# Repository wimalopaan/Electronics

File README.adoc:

= RC Electronics
Wilhelm Meier <wilhelm.wm.meier@googlemail.com>
:toc:
:toclevels: 5
:numbered:
:sectnums:
:sectnumlevels: 5
:toc-placement!:
:tip-caption: :bulb:
:note-caption: :information_source:
:important-caption: :heavy_exclamation_mark:
:caution-caption: :fire:
:warning-caption: :warning:
  
:ddir: https://wimalopaan.github.io/Electronics
:rcb: {ddir}/rc/boards

*English* | <<README.de.adoc#,Deutsch>>

image::images/logo/Logo.png[width=50%]

[NOTE]
--
This page and the accompanying repositories are mostly for my rc (radio controlled models) electronics including EdgeTx/OpenTx and ExpressLRS addons, LUA-scripting, videos, and more.
--

[WARNING]
--
No AI generated code inside, all errors are human!
--

:toclevels: 2
toc::[]

== Foreword

[NOTE]
.To the german readers
--
Die alte Seite ist noch (und bleibt auch) als <<Old.adoc#,Old.adoc>> verfügbar.
--

[[ieee]]
== IEEE: the RC software compound (stack)

Using `EdgeTx`, `ExpressLRS` and `ESCape32` is _the_ combination of RC related open-source software projects that I use 
now in all my crafts. 

[NOTE]
--
The three big `E`s: `EdgeTx`, `ExpressLRS` and `ESCape32` 
--

If I need something like _return-to-home_ I would choose clearly `INAV`. 
So, putting all together, you get `EEEI`.

[IMPORTANT]
--
If you push `EdgeTx`, `ExpressLRS`, `ESCape32` and `INAV` onto a stack, pop them off and take their first character, 
you'll get `IEEE`, the *RC software stack* (please do not confuse with https://www.ieee.org[], that's another crucial thing ;-) ).
--

[[documents]]
== Documents

The content of this page is split into the following documents. The <<detailed_toc>> lists every section with a direct link. The <<project-status>> shows the state of every project. All videos are listed in <<docs/videos.adoc#,Videos by project>>.

=== Software, firmware and protocols

[cols="1,3a",options="header"]
|===
| Document | Contents

| <<docs/edgetx.adoc#,EdgeTx>>
| Extensions and pull-requests for the EdgeTx radio firmware:

* <<docs/edgetx.adoc#edgetx-proc,EdgeTx processing>>
* <<docs/edgetx.adoc#vcontrols,Virtual Controls for EdgeTx>>
* <<docs/edgetx.adoc#edgetx_32channels,32-Channels extension for the CRSF-Protocol>>
* <<docs/edgetx.adoc#edgetx_shm_bw,SHM-Variables for B&W radios>>
* <<docs/edgetx.adoc#crsf_batt_id,Enhanced Parser for instance-id augmented CRSF BATT-sensor frames>>
* <<docs/edgetx.adoc#edgetx_custom_moved,Custom EdgeTx builds>>

| <<docs/elrs.adoc#,ExpressLRS>>
| ExpressLRS: features, modules, receivers and my modifications (V3/V4):

* <<docs/elrs.adoc#_expresslrs_for_short_range_radio_control,ExpressLRS for short range radio control>>
* <<docs/elrs.adoc#_expresslrs_modules_and_receivers,ExpressLRS: modules and receivers>>
* <<docs/elrs.adoc#_multiple_elrs_receivers_bound_to_one_elrs_module,Multiple ELRS-receivers bound to one ELRS-module>>
* <<docs/elrs.adoc#_32_channels_for_elrs,32-channels for ELRS>>
* <<docs/elrs.adoc#elrs-matrix,Feature matrix>>
* <<docs/elrs.adoc#elrs-mods,ELRS modifications and pull-requests>>
* <<docs/elrs.adoc#elrs-relay,ELRS relay configuration>>

| <<docs/protocols.adoc#,Protocols>>
| CRSF protocol extensions (MultiSwitch, Prop32, ESP-NOW), CRSF half-duplex bus, Hardware-Extension-Protocol:

* <<docs/protocols.adoc#crsf_sw,Proposal for the CRSF protocol>>
* <<docs/protocols.adoc#crsf-bus,CRSF-Half-Duplex Bus>>
* <<docs/protocols.adoc#hwext,Hardware-Extension-Protocol>>
* <<docs/protocols.adoc#hwlua,LUA-script for the Hardware-Extension-Protocol>>

| <<docs/escape32.adoc#,ESCape32: firmware for a family of small/medium BLDC (and brushed) motor controller (brushless/brushed ESC)>>
| ESCape32 firmware for small/medium BLDC (and brushed) ESCs and my modifications:

* <<docs/escape32.adoc#_sine_startup,Sine startup>>
* <<docs/escape32.adoc#_modifications,Modifications>>
* <<docs/escape32.adoc#_hardware,Hardware>>
* <<docs/escape32.adoc#_info,Info>>

| <<docs/inav.adoc#,INAV: Navigation-enabled flight control software>>
| INAV and the self-balancing robot Mortimer.

| <<docs/flysky.adoc#,FlySky FS-i6X / FS-i6S>>
| Alternative firmware for FlySky FS-i6X/FS-i6S (Rust and C++), ELRS for the FS-i6X, Openix6:

* <<docs/flysky.adoc#flysky-i6x-rs,FlySky-I6X-rs: an alternative firmware for the FlySky FS-I6X transmitter>>
* <<docs/flysky.adoc#flysky-i6s-rs,FlySky-I6S-rs: an alternative firmware for the FlySky FS-I6S transmitter>>
* <<docs/flysky.adoc#i6s-cpp,i6s-cpp: a C++26 port of the FlySky-I6X-rs / FlySky-I6S-rs firmware>>
* <<docs/flysky.adoc#elrs_i6x,ELRS for the FlySky-I6X>>
* <<docs/flysky.adoc#oix6,Openix6>>

| <<docs/building.adoc#,Building firmware>>
| Compiling my projects (`wmucpp`), EdgeTx, ExpressLRS and ESCape32 with `github` codespaces:

* <<docs/building.adoc#gitpod_wm,Compiling the source code of my projects (`wmucpp`)>>
* <<docs/building.adoc#edgetx_custom,Custom EdgeTx builds>>
* <<docs/building.adoc#build_elrs,ExpressLRS>>
* <<docs/building.adoc#build_escape32,ESCape32>>

|===

=== Projects (hardware and firmware)

[cols="1,3a",options="header"]
|===
| Document | Contents

| <<docs/multiswitch.adoc#,MultiSwitch>>
| ELRS/CRSF MultiSwitch modules, <<docs/multiswitch.adoc#msw_widget_ng,MultiSwitch NG Widget>>, stable MultiSwitch Widget and telemetry script.

| <<docs/crsf-devices.adoc#,CRSF devices>>
| LED 4x4, CRSF-Switch/Router, MultiAdapter, RC-Relay32, CRSF to Serial-Servo converter:

* <<docs/crsf-devices.adoc#led4x4,LED 4x4 Module>>
* <<docs/crsf-devices.adoc#crsf-switch,CRSF-Switch / Router>>
* <<docs/crsf-devices.adoc#elrs_ma,ELRS-MultiAdapter-EA>>
* <<docs/crsf-devices.adoc#rcrelay32,RC-Relay32: a CRSF-Relay>>
* <<docs/crsf-devices.adoc#crsfserialservo,The CRSF to Serial-Servo Converter>>

| <<docs/cruise-control.adoc#,Cruise-Controller>>
| Double Schottel-Control (RC720E) and the CruiseController:

* <<docs/cruise-control.adoc#rc720e,Double Schottel-Control (aka Cruise-Controller)>>
* <<docs/cruise-control.adoc#CC,The `CruiseController`>>

| <<docs/rx-as-tx.adoc#,ELRS receivers as transmitter modules>>
| JR-module-bay adapter and X12S internal adapter for ELRS receivers:

* <<docs/rx-as-tx.adoc#elrs_jr,JR-module-bay adapter for ELRS receiver as transmitter>>
* <<docs/rx-as-tx.adoc#elrs_x12s,Adapter for ELRS receiver as internal XJT/ISRM module for FrSky X12S>>

| <<docs/radio-mods.adoc#,Transmitter modifications>>
| Renewed VarioProp mainboard, X12S touch/sticks, 40MHz module, TX16S switch controller, haptic stick:

* <<docs/radio-mods.adoc#varioprop,Renewed mainboard for some (old) 27/35/40MHz RC transmitters>>
* <<docs/radio-mods.adoc#x12s_touch,Touch-Screen for the FrSky X12S>>
* <<docs/radio-mods.adoc#sfrog,SFrog 5D Sticks for the FrSky X12S>>
* <<docs/radio-mods.adoc#_modification_of_an_old_graupner_jr_40mhz_transmitter_rf_modul_for_use_in_e_g_a_radiomaster_tx16s_frsky_x12sx9e_or_similar,Modification of an old Graupner / JR 40MHz transmitter RF modul for use in e.g. a Radiomaster TX16s / FrSky X12S/X9e or similar>>
* <<docs/radio-mods.adoc#extswitch,The TX16s internal switch controller>>
* <<docs/radio-mods.adoc#haptic,A new kind of stick: haptic-control>>

| <<docs/rc-desk.adoc#,RC-Desk>>
| RC-Desk and RC-Desk mini for TX16S, TX15, X12S, X9E:

* <<docs/rc-desk.adoc#rcdesk,The RC-Desk (for RadioMaster TX16S, FrSky X12S, X9E, ...)>>
* <<docs/rc-desk.adoc#rcdesk32mini,The RC-Desk mini (for RadioMaster TX16S, TX15, FrSky X12S, X9E, ...)>>

| <<docs/motor-controllers.adoc#,Motor controllers>>
| Brushed DC-motor controller and V/ESC:

* <<docs/motor-controllers.adoc#_brushed_dc_motor_controller_with_sensorless_measurement_of_rotational_speed,Brushed DC-motor controller with sensorless measurement of rotational speed>>
* <<docs/motor-controllers.adoc#vesc,V/ESC: the ultimate firmware for medium/big BLDC motor controller (brushless ESC)>>

| <<docs/vhf-receivers.adoc#,Receivers for 27/35/40MHz>>
| Corona RP8D1 replacement firmware and SDR receiver:

* <<docs/vhf-receivers.adoc#corona,Corona RP8D1 replacement firmware>>
* <<docs/vhf-receivers.adoc#sdr,SDR RC receiver for 27/35/40MHz>>

| <<docs/misc.adoc#,Miscellaneous projects>>
| STM32G0B1 development board, simple main power switch:

* <<docs/misc.adoc#devg0b1,WM STM32G0B1 development board>>
* <<docs/misc.adoc#_simple_rc_main_power_latched_switch,Simple RC main power latched switch>>

|===

[[project-status]]
=== Project status

Every project page starts with a _Project info_ box (status, hardware, firmware, software, links).
New projects use the <<docs/project-template.adoc#,project template>>.

.Status legend
[cols="1,4"]
|===
| 🟢 active | under active development
| 🔵 stable | finished and in use; maintenance only
| 🟡 experimental | working partially / under test
| 📝 planned | idea or design, not yet usable
| ⚪ superseded | replaced by another project; kept for reference
|===

[cols="3,2,1",options="header"]
|===
| Project | Document | Status
| <<docs/multiswitch.adoc#mswe8,MultiSwitch-E8>> | <<docs/multiswitch.adoc#,MultiSwitch>> | 🟢 active
| <<docs/multiswitch.adoc#_super_simple_multiswitch_elrscrsf_flyskysbus_flyskyibus_frskysbus_frskys_port_graupnersumdv3,Super simple MultiSwitch>> | <<docs/multiswitch.adoc#,MultiSwitch>> | 🟢 active
| <<docs/multiswitch.adoc#ssmsw,MultiSwitch 16-Outputs PCB>> | <<docs/multiswitch.adoc#,MultiSwitch>> | 🟢 active
| <<docs/multiswitch.adoc#msw_nucleo,Nucleo-G031K8 as a MultiSwitch>> | <<docs/multiswitch.adoc#,MultiSwitch>> | 🟢 active
| <<docs/multiswitch.adoc#msw_weact,WeAct STM32G031F8 as a MultiSwitch>> | <<docs/multiswitch.adoc#,MultiSwitch>> | 🟢 active
| <<docs/multiswitch.adoc#msw_weact_esp32c3,WeAct ESP32-C3 Core Board as a MultiSwitch>> | <<docs/multiswitch.adoc#,MultiSwitch>> | 🟡 experimental
| <<docs/multiswitch.adoc#msw_tht,WeAct MultiSwitch THT PCB>> | <<docs/multiswitch.adoc#,MultiSwitch>> | 🔵 stable
| <<docs/multiswitch.adoc#msw_widget_ng,MultiSwitch NG Widget>> | <<docs/multiswitch.adoc#,MultiSwitch>> | 🟢 active
| <<docs/multiswitch.adoc#msw_widget,MultiSwitch Widget>> | <<docs/multiswitch.adoc#,MultiSwitch>> | 🔵 stable
| <<docs/multiswitch.adoc#msw_bw,MultiSwitch Telemetry Script>> | <<docs/multiswitch.adoc#,MultiSwitch>> | 🔵 stable
| <<docs/crsf-devices.adoc#led4x4,LED 4x4 Module>> | <<docs/crsf-devices.adoc#,CRSF devices>> | 🟢 active
| <<docs/crsf-devices.adoc#crsf-switch,CRSF-Switch / Router>> | <<docs/crsf-devices.adoc#,CRSF devices>> | 🟢 active
| <<docs/crsf-devices.adoc#elrs_ma,ELRS-MultiAdapter-EA>> | <<docs/crsf-devices.adoc#,CRSF devices>> | 🔵 stable
| <<docs/crsf-devices.adoc#rcrelay32,RC-Relay32>> | <<docs/crsf-devices.adoc#,CRSF devices>> | 🟢 active
| <<docs/crsf-devices.adoc#crsfserialservo,CRSF to Serial-Servo Converter>> | <<docs/crsf-devices.adoc#,CRSF devices>> | 🟢 active
| <<docs/cruise-control.adoc#rc720e,Double Schottel-Control / Cruise-Controller (RC720E32)>> | <<docs/cruise-control.adoc#,Cruise-Controller>> | 🟢 active
| <<docs/cruise-control.adoc#CC,The `CruiseController`>> | <<docs/cruise-control.adoc#,Cruise-Controller>> | ⚪ superseded
| <<docs/rc-desk.adoc#rcdesk,RC-Desk>> | <<docs/rc-desk.adoc#,RC-Desk>> | 🟢 active
| <<docs/rc-desk.adoc#rcdesk32mini,RC-Desk mini>> | <<docs/rc-desk.adoc#,RC-Desk>> | 🟢 active
| <<docs/radio-mods.adoc#varioprop,Renewed mainboard for vintage transmitters>> | <<docs/radio-mods.adoc#,Transmitter modifications>> | 🟡 experimental
| <<docs/radio-mods.adoc#x12s_touch,Touch-Screen for the FrSky X12S>> | <<docs/radio-mods.adoc#,Transmitter modifications>> | 🔵 stable
| <<docs/radio-mods.adoc#sfrog,SFrog 5D Sticks for the FrSky X12S>> | <<docs/radio-mods.adoc#,Transmitter modifications>> | 🔵 stable
| <<docs/radio-mods.adoc#_modification_of_an_old_graupner_jr_40mhz_transmitter_rf_modul_for_use_in_e_g_a_radiomaster_tx16s_frsky_x12sx9e_or_similar,Graupner / JR 40MHz RF module for modern radios>> | <<docs/radio-mods.adoc#,Transmitter modifications>> | 🔵 stable
| <<docs/radio-mods.adoc#extswitch,TX16s internal switch controller>> | <<docs/radio-mods.adoc#,Transmitter modifications>> | 🔵 stable
| <<docs/radio-mods.adoc#haptic,Haptic-control stick>> | <<docs/radio-mods.adoc#,Transmitter modifications>> | 📝 planned
| <<docs/rx-as-tx.adoc#elrs_jr,JR-module-bay adapter for ELRS RX-as-TX>> | <<docs/rx-as-tx.adoc#,RX-as-TX>> | 🔵 stable
| <<docs/rx-as-tx.adoc#elrs_x12s,X12S internal ELRS adapter>> | <<docs/rx-as-tx.adoc#,RX-as-TX>> | 🔵 stable
| <<docs/flysky.adoc#flysky-i6x-rs,FlySky-I6X-rs>> | <<docs/flysky.adoc#,FlySky>> | 🟢 active
| <<docs/flysky.adoc#flysky-i6s-rs,FlySky-I6S-rs>> | <<docs/flysky.adoc#,FlySky>> | 🟢 active
| <<docs/flysky.adoc#i6s-cpp,i6s-cpp (C++26 port)>> | <<docs/flysky.adoc#,FlySky>> | 🟢 active
| <<docs/flysky.adoc#elrs_i6x,ELRS for the FlySky-I6X>> | <<docs/flysky.adoc#,FlySky>> | 🔵 stable
| <<docs/flysky.adoc#oix6,Openix6>> | <<docs/flysky.adoc#,FlySky>> | 🔵 stable
| <<docs/motor-controllers.adoc#_brushed_dc_motor_controller_with_sensorless_measurement_of_rotational_speed,Brushed DC-motor controller>> | <<docs/motor-controllers.adoc#,Motor controllers>> | 🟡 experimental
| <<docs/motor-controllers.adoc#vesc,V/ESC>> | <<docs/motor-controllers.adoc#,Motor controllers>> | 🟢 active
| <<docs/vhf-receivers.adoc#corona,Corona RP8D1 replacement firmware>> | <<docs/vhf-receivers.adoc#,VHF receivers>> | 🔵 stable
| <<docs/vhf-receivers.adoc#sdr,SDR RC receiver for 27/35/40MHz>> | <<docs/vhf-receivers.adoc#,VHF receivers>> | 🟡 experimental
| <<docs/misc.adoc#devg0b1,WM STM32G0B1 development board>> | <<docs/misc.adoc#,Misc>> | 🔵 stable
| <<docs/misc.adoc#_simple_rc_main_power_latched_switch,Simple RC main power latched switch>> | <<docs/misc.adoc#,Misc>> | 🔵 stable
| <<docs/inav.adoc#mortimer,Mortimer (self-balancing robot)>> | <<docs/inav.adoc#,INAV>> | 🟡 experimental
| <<docs/edgetx.adoc#vcontrols,EdgeTx: Virtual Controls>> | <<docs/edgetx.adoc#,EdgeTx>> | 🟢 active
| <<docs/edgetx.adoc#edgetx_32channels,EdgeTx: 32-channels extension>> | <<docs/edgetx.adoc#,EdgeTx>> | 🟢 active
| <<docs/edgetx.adoc#edgetx_shm_bw,EdgeTx: SHM-Variables for B&W radios>> | <<docs/edgetx.adoc#,EdgeTx>> | 🔵 stable
| <<docs/edgetx.adoc#crsf_batt_id,EdgeTx: CRSF BATT frames with sensor-id>> | <<docs/edgetx.adoc#,EdgeTx>> | 🟢 active
| <<docs/escape32.adoc#,ESCape32 (modifications)>> | <<docs/escape32.adoc#,ESCape32>> | 🟢 active
|===

=== Gear

[cols="1,3a",options="header"]
|===
| Document | Contents

| <<docs/gear.adoc#,Actual gear>>
| My actual RC gear and modifications:

* <<docs/gear.adoc#_radiomaster,RadioMaster>>
* <<docs/gear.adoc#_flysky,FlySky>>
* <<docs/gear.adoc#_jumper,Jumper>>
* <<docs/gear.adoc#_frsky,FrSky>>
* <<docs/gear.adoc#_graupnersj,Graupner/SJ>>

| <<docs/vintage.adoc#,Vintage RC>>
| Vintage RC equipment:

* <<docs/vintage.adoc#_graupner_grundig_jr,Graupner / Grundig / JR>>
* <<docs/vintage.adoc#_robbe_futaba,Robbe / Futaba>>
* <<docs/vintage.adoc#_other_3,Other>>

|===

== Projects

The documents listed in <<documents>> describe some of my active projects. The majority of my former projects (see <<Old.adoc#,Old>> (in german)) are
in a frozen state now. This is due to the fact that I completely shifted the µCs from the AVR-family (DA, DB, tiny1/2) to the more powerful 
STM32-family, mainly the STM32G4xx and STM32G0xx. These have enough computing resources for the <<docs/vhf-receivers.adoc#sdr,SDR RC receiver for 27/35/40MHz>> project, which would have been impossible sticking to 
the AVRs. And the G0xx also have enough internal peripheral to comfy realize all that crazy rc stuff.

Well, there is one exception: the <<docs/vhf-receivers.adoc#corona,Corona RP8D1 replacement firmware>>.

[[trademark]]
=== Logo

Despite the fact that I publish all my projects as open-hardware (mostly CC licensed) and open-source (most GPLV3 licensed)
I use the following _logo_ on the physical projects.

.Logo (License of the logo: https://creativecommons.org/licenses/by-nc-nd/4.0[CC BY-NC-ND 4.0]) (click to enlarge)
image::images/logo/Logo.png[width=240, link="images/logo/Logo.png"]

[[oshwlab]]
=== Hardware designs available on OSHWLab

An increasing number of PCB designs are available on https://oshwlab.com/wilhelm.wm.meier/works[OSHWLab]. 

== OpenTx / EdgeTx weekly

_OpenTx weekly_ is a https://www.youtube.com/channel/UCedl1hS-dfWh-V4WBz_jGog[YouTube]-channel mostly 
for EdgeTx and OpenTx stuff but also for my above electronic projects. Unfortunately the spoken language is german :-( 

All videos of the channel, sorted by project: <<docs/videos.adoc#,Videos by project>>.
Every _Project info_ box also lists the videos of the project.

On https://schiffsmodell.blogspot.com/p/grundlagen-zu-opentx.html[Holger Meyer] you may find an up-to-date table of contents.

[[detailed_toc]]
== Detailed table of contents

[[dtoc]]All sections of the former single-page README with a link to their new location. The anchors of the former page are kept here, so old links like `README.adoc#elrs-mods-v4` still lead to the right place.

* [[edgetx]]<<docs/edgetx.adoc#,EdgeTx>>
** [[edgetx-proc]]<<docs/edgetx.adoc#edgetx-proc,EdgeTx processing>>
** [[vcontrols]]<<docs/edgetx.adoc#vcontrols,Virtual Controls for EdgeTx>>
** [[edgetx_32channels]]<<docs/edgetx.adoc#edgetx_32channels,32-Channels extension for the CRSF-Protocol>>
** [[edgetx_shm_bw]]<<docs/edgetx.adoc#edgetx_shm_bw,SHM-Variables for B&W radios>>
** [[crsf_batt_id]]<<docs/edgetx.adoc#crsf_batt_id,Enhanced Parser for instance-id augmented CRSF BATT-sensor frames>>
** [[edgetx_custom]]<<docs/building.adoc#edgetx_custom,Custom EdgeTx builds>>
*** [[_setting_up_gitpod_not_recommended]]<<docs/building.adoc#_setting_up_gitpod_not_recommended,Setting up `gitpod` (not recommended)>>
*** [[compiling_edgetx]]<<docs/building.adoc#compiling_edgetx,Compiling EdgeTx>>
* [[elrs]]<<docs/elrs.adoc#,ExpressLRS>>
** [[_expresslrs_for_short_range_radio_control]][[elrs_feat]][[elrs_func]]<<docs/elrs.adoc#_expresslrs_for_short_range_radio_control,ExpressLRS for short range radio control>>
** [[crsf_sw]]<<docs/protocols.adoc#crsf_sw,Proposal for the CRSF protocol>>
*** [[crsf-frame]]<<docs/protocols.adoc#crsf-frame,Frame structure>>
**** [[_general_crsf_frame]]<<docs/protocols.adoc#_general_crsf_frame,General CRSF frame>>
**** [[crsf-cmd-frame]]<<docs/protocols.adoc#crsf-cmd-frame,Command frame (type `0x32`)>>
*** [[crsf-sw]]<<docs/protocols.adoc#crsf-sw,Commands for MultiSwitch (realm `0xa1`)>>
**** [[_command_0x01_set]]<<docs/protocols.adoc#_command_0x01_set,Command `0x01` (Set)>>
**** [[_command_0x07_set4]]<<docs/protocols.adoc#_command_0x07_set4,Command `0x07` (Set4)>>
**** [[_command_0x09_set4m]]<<docs/protocols.adoc#_command_0x09_set4m,Command `0x09` (Set4M)>>
**** [[_command_0x02_prop]]<<docs/protocols.adoc#_command_0x02_prop,Command `0x02` (Prop)>>
**** [[_command_0x0a_setrgb]]<<docs/protocols.adoc#_command_0x0a_setrgb,Command `0x0a` (setRGB)>>
**** [[_command_0x11_intermodule_pattern_start]]<<docs/protocols.adoc#_command_0x11_intermodule_pattern_start,Command `0x11` (intermodule pattern start)>>
**** [[_command_0x12_intermodule_pattern_stop_all]]<<docs/protocols.adoc#_command_0x12_intermodule_pattern_stop_all,Command `0x12` (intermodule pattern stop all)>>
**** [[_command_0x13_intermodule_slave_set]]<<docs/protocols.adoc#_command_0x13_intermodule_slave_set,Command `0x13` (intermodule slave set)>>
*** [[prop32]]<<docs/protocols.adoc#prop32,Proportional data (e.g. additional channels: >=8bit)>>
*** [[_telemetry_passthrough_messages]]<<docs/protocols.adoc#_telemetry_passthrough_messages,Telemetry passthrough messages>>
*** [[crsf-esp-now]]<<docs/protocols.adoc#crsf-esp-now,CRSF over ESP-NOW>>
** [[_expresslrs_modules_and_receivers]][[hm_es24tx]][[hm_ep1ep2]][[rm_er6]]<<docs/elrs.adoc#_expresslrs_modules_and_receivers,ExpressLRS: modules and receivers>>
** [[_multiple_elrs_receivers_bound_to_one_elrs_module]]<<docs/elrs.adoc#_multiple_elrs_receivers_bound_to_one_elrs_module,Multiple ELRS-receivers bound to one ELRS-module>>
** [[_32_channels_for_elrs]]<<docs/elrs.adoc#_32_channels_for_elrs,32-channels for ELRS>>
** [[elrs-matrix]]<<docs/elrs.adoc#elrs-matrix,Feature matrix>>
** [[elrs-mods]]<<docs/elrs.adoc#elrs-mods,ELRS modifications and pull-requests>>
*** [[elrs-mods-v4]]<<docs/elrs.adoc#elrs-mods-v4,ExpressLRS V4>>
*** [[elrs-ch32]]<<docs/elrs.adoc#elrs-ch32,32-channels extension for ELRS V4>>
*** [[elrs-escape32]]<<docs/elrs.adoc#elrs-escape32,Support for flashing / setup of `ESCape32` ESCs>>
*** [[elrs-3rd-serial]]<<docs/elrs.adoc#elrs-3rd-serial,Third serial interface for ELRS V4>>
*** [[elrs-esp-now]]<<docs/elrs.adoc#elrs-esp-now,CRSF-over-ESP-NOW for ELRS V4>>
*** [[elrs-esp-bridge]]<<docs/elrs.adoc#elrs-esp-bridge,ESP32C3-mini as USB/ESP-NOW-Bridge>>
*** [[elrs-rxtx-analog]]<<docs/elrs.adoc#elrs-rxtx-analog,ELRS-receiver as TX-module with direct analog inputs>>
*** [[elrs-tx-relay]]<<docs/elrs.adoc#elrs-tx-relay,ELRS-Transmitter as CRSF-Relay in ELRS V4>>
*** [[elrs-io-expand]]<<docs/elrs.adoc#elrs-io-expand,ELRS-receiver with I2C IO-expander for MultiSwitch in ELRS V4>>
*** [[_elrs_v3_modifications]]<<docs/elrs.adoc#_elrs_v3_modifications,ELRS V3 Modifications>>
**** [[elrs-route]]<<docs/elrs.adoc#elrs-route,Allow other than `0xc8` as extended addresses (Version 3.x.x only)>>
**** [[elrs_cs]]<<docs/building.adoc#elrs_cs,Use `github` codespaces to compile ExpressLRS>>
**** [[_use_gitpod_to_compile_expresslrs_not_recommended]]<<docs/building.adoc#_use_gitpod_to_compile_expresslrs_not_recommended,Use `gitpod` to compile ExpressLRS (not recommended)>>
**** [[elrs_compile]]<<docs/building.adoc#elrs_compile,Compilation>>
**** [[elrs_arm4]]<<docs/elrs.adoc#elrs_arm4,ELRS4 new arming method for version 3  (Version 3.x.x only)>>
**** [[elrs_perm_arm]]<<docs/elrs.adoc#elrs_perm_arm,ELRS4 permanent arming (Version 3.x.x only)>>
**** [[elrs_sbus_flip]]<<docs/elrs.adoc#elrs_sbus_flip,ELRS, 32-channels and SBus-Output (with channel flipping)  (Version 3.x.x only)>>
*** [[elrs_sumdv3]]<<docs/elrs.adoc#elrs_sumdv3,ELRS, SumDV3 and MultiSwitch (V4 and V3)>>
*** [[elrs_pwm_msw]]<<docs/elrs.adoc#elrs_pwm_msw,Use an ELRS PWM-receiver as MultiSwitch>>
*** [[elrs_combined]]<<docs/elrs.adoc#elrs_combined,Combined ELRS modifications>>
**** [[_multiple_crsf_devices_connected_to_a_receiver]][[elrs_v4]]<<docs/elrs.adoc#elrs_v4,Multiple CRSF devices connected to a receiver>>
* [[escape32]]<<docs/escape32.adoc#,ESCape32: firmware for a family of small/medium BLDC (and brushed) motor controller (brushless/brushed ESC)>>
** [[_sine_startup]]<<docs/escape32.adoc#_sine_startup,Sine startup>>
** [[_modifications]]<<docs/escape32.adoc#_modifications,Modifications>>
*** [[esc32_mod]]<<docs/building.adoc#esc32_mod,Compile modified `ESCape32` in `github codespace`>>
*** [[esc32_batt]]<<docs/escape32.adoc#esc32_batt,Augmented `BATT` telemetry frames (CRSF)>>
** [[_hardware]]<<docs/escape32.adoc#_hardware,Hardware>>
** [[_info]]<<docs/escape32.adoc#_info,Info>>
* [[flysky-i6x-rs]]<<docs/flysky.adoc#flysky-i6x-rs,FlySky-I6X-rs: an alternative firmware for the FlySky FS-I6X transmitter>>
** [[_hardware_modifications]]<<docs/flysky.adoc#_hardware_modifications,Hardware-Modifications>>
** [[_images_of_hardware_modifications]]<<docs/flysky.adoc#_images_of_hardware_modifications,Images of hardware-modifications>>
* [[flysky-i6s-rs]]<<docs/flysky.adoc#flysky-i6s-rs,FlySky-I6S-rs: an alternative firmware for the FlySky FS-I6S transmitter>>
** [[_hardware_modifications_2]]<<docs/flysky.adoc#_hardware_modifications_2,Hardware-Modifications>>
** [[_images_of_hardware_modifications_2]]<<docs/flysky.adoc#_images_of_hardware_modifications_2,Images of hardware-modifications>>
* [[i6s-cpp]]<<docs/flysky.adoc#i6s-cpp,i6s-cpp: a C++26 port of the FlySky-I6X-rs / FlySky-I6S-rs firmware>>
** [[i6s-cpp-design]]<<docs/flysky.adoc#i6s-cpp-design,Design>>
** [[i6s-cpp-features]]<<docs/flysky.adoc#i6s-cpp-features,Features>>
** [[i6s-cpp-deviations]]<<docs/flysky.adoc#i6s-cpp-deviations,Differences from the Rust firmware>>
** [[i6s-cpp-build]]<<docs/flysky.adoc#i6s-cpp-build,Building>>
* [[inav]]<<docs/inav.adoc#,INAV: Navigation-enabled flight control software>>
** [[gitpod_wm]]<<docs/building.adoc#gitpod_wm,Compiling the source code of my projects (`wmucpp`)>>
*** [[cs_wm]]<<docs/building.adoc#cs_wm,Using `github` CodeSpaces>>
*** [[_using_gitpod_not_recommended]]<<docs/building.adoc#_using_gitpod_not_recommended,Using `gitpod` (not recommended)>>
** [[corona]]<<docs/vhf-receivers.adoc#corona,Corona RP8D1 replacement firmware>>
** [[varioprop]]<<docs/radio-mods.adoc#varioprop,Renewed mainboard for some (old) 27/35/40MHz RC transmitters>>
*** [[_the_new_mainboard]]<<docs/radio-mods.adoc#_the_new_mainboard,The new mainboard>>
**** [[_previous_versions_of_the_new_mainboard]][[VarNG02]][[VarNG03]][[VarNG03pcbtop]][[VarNG03pcbbot]][[hardsw]][[gausssw]][[f14spec]][[grspec]]<<docs/radio-mods.adoc#_previous_versions_of_the_new_mainboard,Previous versions of the new mainboard>>
*** [[_the_new_switches_board]]<<docs/radio-mods.adoc#_the_new_switches_board,The new switches-board>>
*** [[_remote_control_the_remote_control_via_bluetooth]]<<docs/radio-mods.adoc#_remote_control_the_remote_control_via_bluetooth,Remote control the remote control via BlueTooth>>
*** [[_inside_the_housing]]<<docs/radio-mods.adoc#_inside_the_housing,Inside the housing>>
** [[sdr]]<<docs/vhf-receivers.adoc#sdr,SDR RC receiver for 27/35/40MHz>>
** [[x12s_touch]]<<docs/radio-mods.adoc#x12s_touch,Touch-Screen for the FrSky X12S>>
** [[sfrog]]<<docs/radio-mods.adoc#sfrog,SFrog 5D Sticks for the FrSky X12S>>
** [[_modification_of_an_old_graupner_jr_40mhz_transmitter_rf_modul_for_use_in_e_g_a_radiomaster_tx16s_frsky_x12sx9e_or_similar]]<<docs/radio-mods.adoc#_modification_of_an_old_graupner_jr_40mhz_transmitter_rf_modul_for_use_in_e_g_a_radiomaster_tx16s_frsky_x12sx9e_or_similar,Modification of an old Graupner / JR 40MHz transmitter RF modul for use in e.g. a Radiomaster TX16s / FrSky X12S/X9e or similar>>
** [[_brushed_dc_motor_controller_with_sensorless_measurement_of_rotational_speed]]<<docs/motor-controllers.adoc#_brushed_dc_motor_controller_with_sensorless_measurement_of_rotational_speed,Brushed DC-motor controller with sensorless measurement of rotational speed>>
*** [[_rotational_speed_measurement]]<<docs/motor-controllers.adoc#_rotational_speed_measurement,Rotational speed measurement>>
*** [[_version_1_max_8a_36v]]<<docs/motor-controllers.adoc#_version_1_max_8a_36v,Version 1: max. 8A / 36V>>
**** [[bdc_S_sch]]<<docs/motor-controllers.adoc#bdc_S_sch,Schematic and PCB>>
**** [[_images]]<<docs/motor-controllers.adoc#_images,Images>>
*** [[_version_2_max_50a_36v]]<<docs/motor-controllers.adoc#_version_2_max_50a_36v,Version 2: max. 50A / 36V>>
**** [[_µc_module]]<<docs/motor-controllers.adoc#_µc_module,µC module>>
**** [[_power_module]]<<docs/motor-controllers.adoc#_power_module,Power module>>
**** [[_images_2]]<<docs/motor-controllers.adoc#_images_2,Images>>
** [[vesc]]<<docs/motor-controllers.adoc#vesc,V/ESC: the ultimate firmware for medium/big BLDC motor controller (brushless ESC)>>
** [[elrs_jr]]<<docs/rx-as-tx.adoc#elrs_jr,JR-module-bay adapter for ELRS receiver as transmitter>>
*** [[_using_elrs_receivers_as_transmitter_modules]]<<docs/rx-as-tx.adoc#_using_elrs_receivers_as_transmitter_modules,Using ELRS receivers as transmitter-modules>>
*** [[_esp8285_based_receivers]][[elrs_esp8285]]<<docs/rx-as-tx.adoc#_esp8285_based_receivers,ESP8285-based receivers>>
*** [[_esp32_and_esp32c3_based_receivers]]<<docs/rx-as-tx.adoc#_esp32_and_esp32c3_based_receivers,ESP32 and ESP32C3-based receivers>>
**** [[_using_expresslrs_configurator_to_flash_an_esp32c3_receiver_as_a_transmitter]][[elrs_esp32]]<<docs/rx-as-tx.adoc#_using_expresslrs_configurator_to_flash_an_esp32c3_receiver_as_a_transmitter,Using `expresslrs-configurator` to flash an ESP32/C3 receiver as a transmitter>>
**** [[_using_platformio_cli_to_flash_an_esp32c3_receiver_as_a_transmitter]]<<docs/rx-as-tx.adoc#_using_platformio_cli_to_flash_an_esp32c3_receiver_as_a_transmitter,Using `platformio` `cli` to flash an ESP32/C3 receiver as a transmitter>>
**** [[_outdated_information]]<<docs/rx-as-tx.adoc#_outdated_information,Outdated information>>
*** [[_jr_module_bay_adapter]][[jr_elrs_sch]][[jr_elrs_pcb]][[jr_elrs_target]][[jr_elrs_la]]<<docs/rx-as-tx.adoc#_jr_module_bay_adapter,JR-Module-bay adapter>>
*** [[_assembling]]<<docs/rx-as-tx.adoc#_assembling,Assembling>>
*** [[_usages]]<<docs/rx-as-tx.adoc#_usages,Usages>>
**** [[_jumper_t12]]<<docs/rx-as-tx.adoc#_jumper_t12,Jumper T12>>
**** [[_frsky_x9e]]<<docs/rx-as-tx.adoc#_frsky_x9e,FrSky X9e>>
** [[elrs_x12s]][[x12s_elrs_target]][[x12s_elrs_sch]][[x12s_elrs_pcb]]<<docs/rx-as-tx.adoc#elrs_x12s,Adapter for ELRS receiver as internal XJT/ISRM module for FrSky X12S>>
** [[elrs_i6x]][[elrx_i6x]]<<docs/flysky.adoc#elrs_i6x,ELRS for the FlySky-I6X>>
*** [[_since_version_1_13]]<<docs/flysky.adoc#_since_version_1_13,Since Version `1.13`>>
*** [[_before_version_1_13]]<<docs/flysky.adoc#_before_version_1_13,Before Version `1.13`>>
*** [[_images_wiring_and_schematic]]<<docs/flysky.adoc#_images_wiring_and_schematic,Images, wiring and schematic>>
** [[elrs_msw]]<<docs/multiswitch.adoc#elrs_msw,ELRS-MultiSwitch>>
*** [[_in_the_old_days]]<<docs/multiswitch.adoc#_in_the_old_days,In the old days>>
*** [[_new_elrs_version]]<<docs/multiswitch.adoc#_new_elrs_version,New ELRS version>>
**** [[_overview]]<<docs/multiswitch.adoc#_overview,Overview>>
**** [[_puzzeling_parts]]<<docs/multiswitch.adoc#_puzzling_parts,Puzzling parts>>
**** [[_design]]<<docs/multiswitch.adoc#_design,Design>>
**** [[mswe8]]<<docs/multiswitch.adoc#mswe8,MultiSwitch-E8>>
**** [[_housing]]<<docs/multiswitch.adoc#_housing,Housing>>
**** [[_super_simple_multiswitch_elrscrsf_flyskysbus_flyskyibus_frskysbus_frskys_port_graupnersumdv3]]<<docs/multiswitch.adoc#_super_simple_multiswitch_elrscrsf_flyskysbus_flyskyibus_frskysbus_frskys_port_graupnersumdv3,Super simple MultiSwitch (ELRS/CRSF, FlySky/SBus, FlySky/IBus, FrSky/SBus, FrSky/S.Port, Graupner/SumDV3)>>
**** [[ssmsw]]<<docs/multiswitch.adoc#ssmsw,16-Outputs PCB>>
**** [[msw_nucleo]]<<docs/multiswitch.adoc#msw_nucleo,STM32G031F8 Nucleo-Board as a MultiSwitch>>
**** [[msw_weact]]<<docs/multiswitch.adoc#msw_weact,WeAct STM32G031F8 as a MultiSwitch>>
**** [[msw_weact_esp32c3]]<<docs/multiswitch.adoc#msw_weact_esp32c3,WeAct ESP32-C3 Core Board as a MultiSwitch>>
**** [[msw_tht]]<<docs/multiswitch.adoc#msw_tht,WeAct STM32G031F8 as a MultiSwitch with PCB as THT>>
**** [[msw_widget_ng]]<<docs/multiswitch.adoc#msw_widget_ng,MultiSwitch NG Widget>>
**** [[msw_widget]]<<docs/multiswitch.adoc#msw_widget,MultiSwitch Widget>>
**** [[msw_bw]]<<docs/multiswitch.adoc#msw_bw,MultiSwitch Telemetry Script>>
**** [[crsf_enc]]<<docs/multiswitch.adoc#crsf_enc,CRSF encoding>>
**** [[sport_enc]]<<docs/multiswitch.adoc#sport_enc,S.Port encoding>>
**** [[sbus_enc]]<<docs/multiswitch.adoc#sbus_enc,SBus simple (unreliable) encoding>>
** [[led4x4]]<<docs/crsf-devices.adoc#led4x4,LED 4x4 Module>>
*** [[_schematic]]<<docs/crsf-devices.adoc#_schematic,Schematic>>
*** [[_pcb]]<<docs/crsf-devices.adoc#_pcb,PCB>>
*** [[_firmware]]<<docs/crsf-devices.adoc#_firmware,Firmware>>
*** [[_production_data]]<<docs/crsf-devices.adoc#_production_data,Production data>>
** [[crsf-bus]][[crsf_hd_scheme]]<<docs/protocols.adoc#crsf-bus,CRSF-Half-Duplex Bus>>
*** [[_demo_video]]<<docs/protocols.adoc#_demo_video,Demo (Video)>>
** [[rc720e]]<<docs/cruise-control.adoc#rc720e,Double Schottel-Control (aka Cruise-Controller)>>
*** [[_demo_video_2]]<<docs/cruise-control.adoc#_demo_video,Demo (Video)>>
*** [[_schematics]]<<docs/cruise-control.adoc#_schematics,Schematics>>
*** [[_pcb_2]]<<docs/cruise-control.adoc#_pcb,PCB>>
*** [[_firmware_2]]<<docs/cruise-control.adoc#_firmware,Firmware>>
*** [[_widget]]<<docs/cruise-control.adoc#_widget,Widget>>
** [[crsf-switch]]<<docs/crsf-devices.adoc#crsf-switch,CRSF-Switch / Router>>
** [[elrs-relay]]<<docs/elrs.adoc#elrs-relay,ELRS relay configuration>>
** [[elrs_ma]]<<docs/crsf-devices.adoc#elrs_ma,ELRS-MultiAdapter-EA>>
** [[CC]]<<docs/cruise-control.adoc#CC,The `CruiseController`>>
** [[hwext]]<<docs/protocols.adoc#hwext,Hardware-Extension-Protocol>>
*** [[_physical_layer]]<<docs/protocols.adoc#_physical_layer,Physical layer>>
*** [[_application_layer]]<<docs/protocols.adoc#_application_layer,Application Layer>>
**** [[_packet_format]]<<docs/protocols.adoc#_packet_format,Packet Format>>
**** [[hwext_timing]]<<docs/protocols.adoc#hwext_timing,Multi-Master Timing>>
** [[hwlua]]<<docs/protocols.adoc#hwlua,LUA-script for the Hardware-Extension-Protocol>>
*** [[_new_version_of_the_lua_script_for_the_hardware_extension_protocol]]<<docs/protocols.adoc#_new_version_of_the_lua_script_for_the_hardware_extension_protocol,New version of the LUA-script for the Hardware-Extension-Protocol>>
*** [[_old_version]][[hwluaimg1]][[hwluaimg2]]<<docs/protocols.adoc#_old_version,Old version>>
** [[extswitch]][[hwattiny1]][[hwattiny2]][[hwattiny3]][[hwattiny4]]<<docs/radio-mods.adoc#extswitch,The TX16s internal switch controller>>
*** [[_code]]<<docs/radio-mods.adoc#_code,Code>>
*** [[_stick_end_switches]]<<docs/radio-mods.adoc#_stick_end_switches,Stick-End Switches>>
** [[rcdesk]]<<docs/rc-desk.adoc#rcdesk,The RC-Desk (for RadioMaster TX16S, FrSky X12S, X9E, ...)>>
** [[rcdesk32mini]]<<docs/rc-desk.adoc#rcdesk32mini,The RC-Desk mini (for RadioMaster TX16S, TX15, FrSky X12S, X9E, ...)>>
** [[rcrelay32]][[relay_img01]][[relay_img02]][[relay_img03]][[relay_menu04]][[relay_menu01]][[relay_menu02]][[relay_menu03]]<<docs/crsf-devices.adoc#rcrelay32,RC-Relay32: a CRSF-Relay>>
*** [[multi-part-model]]<<docs/crsf-devices.adoc#multi-part-model,The Multipart-Model problem>>
** [[devg0b1]][[devg0b1img]]<<docs/misc.adoc#devg0b1,WM STM32G0B1 development board>>
** [[crsfserialservo]][[serialservo01]][[serialservo02]][[serialservo03]]<<docs/crsf-devices.adoc#crsfserialservo,The CRSF to Serial-Servo Converter>>
** [[mortimer]]<<docs/inav.adoc#mortimer,Self-balancing inverted pendulum robot with INav (Project: Mortimer)>>
** [[haptic]]<<docs/radio-mods.adoc#haptic,A new kind of stick: haptic-control>>
** [[_simple_rc_main_power_latched_switch]]<<docs/misc.adoc#_simple_rc_main_power_latched_switch,Simple RC main power latched switch>>
* [[oix6]]<<docs/flysky.adoc#oix6,Openix6>>
** [[_firmware_3]]<<docs/flysky.adoc#_firmware,Firmware>>
** [[_compiling]]<<docs/flysky.adoc#_compiling,Compiling>>
** [[_flashing]]<<docs/flysky.adoc#_flashing,Flashing>>
* [[gear]]<<docs/gear.adoc#,Actual gear>>
** [[_radiomaster]]<<docs/gear.adoc#_radiomaster,RadioMaster>>
*** [[_tx16s_mk3]]<<docs/gear.adoc#_tx16s_mk3,TX16S MK3>>
*** [[_tx15]]<<docs/gear.adoc#_tx15,TX15>>
*** [[_mt12]]<<docs/gear.adoc#_mt12,MT12>>
*** [[_tx16s]]<<docs/gear.adoc#_tx16s,TX16S>>
*** [[_desk_for_the_tx16s]]<<docs/gear.adoc#_desk_for_the_tx16s,Desk for the TX16s>>
** [[_flysky]]<<docs/gear.adoc#_flysky,FlySky>>
*** [[_fs_i6x]]<<docs/gear.adoc#_fs_i6x,FS-i6X>>
** [[_jumper]]<<docs/gear.adoc#_jumper,Jumper>>
*** [[_t12]]<<docs/gear.adoc#_t12,T12>>
** [[_frsky]]<<docs/gear.adoc#_frsky,FrSky>>
*** [[_x9e]]<<docs/gear.adoc#_x9e,X9e>>
*** [[_x12s]]<<docs/gear.adoc#_x12s,X12S>>
** [[_graupnersj]]<<docs/gear.adoc#_graupnersj,Graupner/SJ>>
*** [[_mc_16]]<<docs/gear.adoc#_mc_16,MC-16>>
* [[vintage]]<<docs/vintage.adoc#,Vintage RC>>
** [[_graupner_grundig_jr]]<<docs/vintage.adoc#_graupner_grundig_jr,Graupner / Grundig / JR>>
*** [[gr_txs]][[varioprop_black]][[varioprop_yellow]][[varioprop_red]]<<docs/vintage.adoc#gr_txs,Transmitter>>
*** [[_receiver]]<<docs/vintage.adoc#_receiver,Receiver>>
*** [[_other]]<<docs/vintage.adoc#_other,Other>>
** [[_robbe_futaba]]<<docs/vintage.adoc#_robbe_futaba,Robbe / Futaba>>
*** [[rb_txs]][[robbe_f14]]<<docs/vintage.adoc#rb_txs,Transmitter>>
*** [[_receiver_2]]<<docs/vintage.adoc#_receiver_2,Receiver>>
*** [[_other_2]]<<docs/vintage.adoc#_other_2,Other>>
** [[_other_3]]<<docs/vintage.adoc#_other_3,Other>>
*** [[_transmitter]]<<docs/vintage.adoc#_transmitter,Transmitter>>
*** [[_receiver_3]]<<docs/vintage.adoc#_receiver_3,Receiver>>
*** [[_other_4]]<<docs/vintage.adoc#_other_4,Other>>
* [[videos]]<<docs/videos.adoc#,Videos by project>>
** [[vg-crsf-devices]]<<docs/videos.adoc#vg-crsf-devices,CRSF devices>>
** [[vg-multiswitch]]<<docs/videos.adoc#vg-multiswitch,MultiSwitch>>
** [[vg-cruise-control]]<<docs/videos.adoc#vg-cruise-control,Cruise-Controller>>
** [[vg-elrs]]<<docs/videos.adoc#vg-elrs,ExpressLRS>>
** [[vg-rx-as-tx]]<<docs/videos.adoc#vg-rx-as-tx,ELRS receivers as transmitter modules>>
** [[vg-edgetx]]<<docs/videos.adoc#vg-edgetx,EdgeTx and protocols>>
** [[vg-flysky]]<<docs/videos.adoc#vg-flysky,FlySky>>
** [[vg-inav]]<<docs/videos.adoc#vg-inav,INAV>>
** [[vg-motor-controllers]]<<docs/videos.adoc#vg-motor-controllers,Motor controllers>>
** [[vg-rc-desk]]<<docs/videos.adoc#vg-rc-desk,RC-Desk>>
** [[vg-radio-mods]]<<docs/videos.adoc#vg-radio-mods,Transmitter modifications>>
** [[vg-vhf]]<<docs/videos.adoc#vg-vhf,Receivers for 27/35/40MHz>>
** [[vg-misc]]<<docs/videos.adoc#vg-misc,Miscellaneous>>
** [[vg-weekly]]<<docs/videos.adoc#vg-weekly,OpenTx / EdgeTx weekly (tutorials)>>

== License

Please see link:LICENSE[License], as far as not other licenses apply (e.g. in the source code).

== Contact

mailto:wilhelm.wm.meier@googlemail.com[email]

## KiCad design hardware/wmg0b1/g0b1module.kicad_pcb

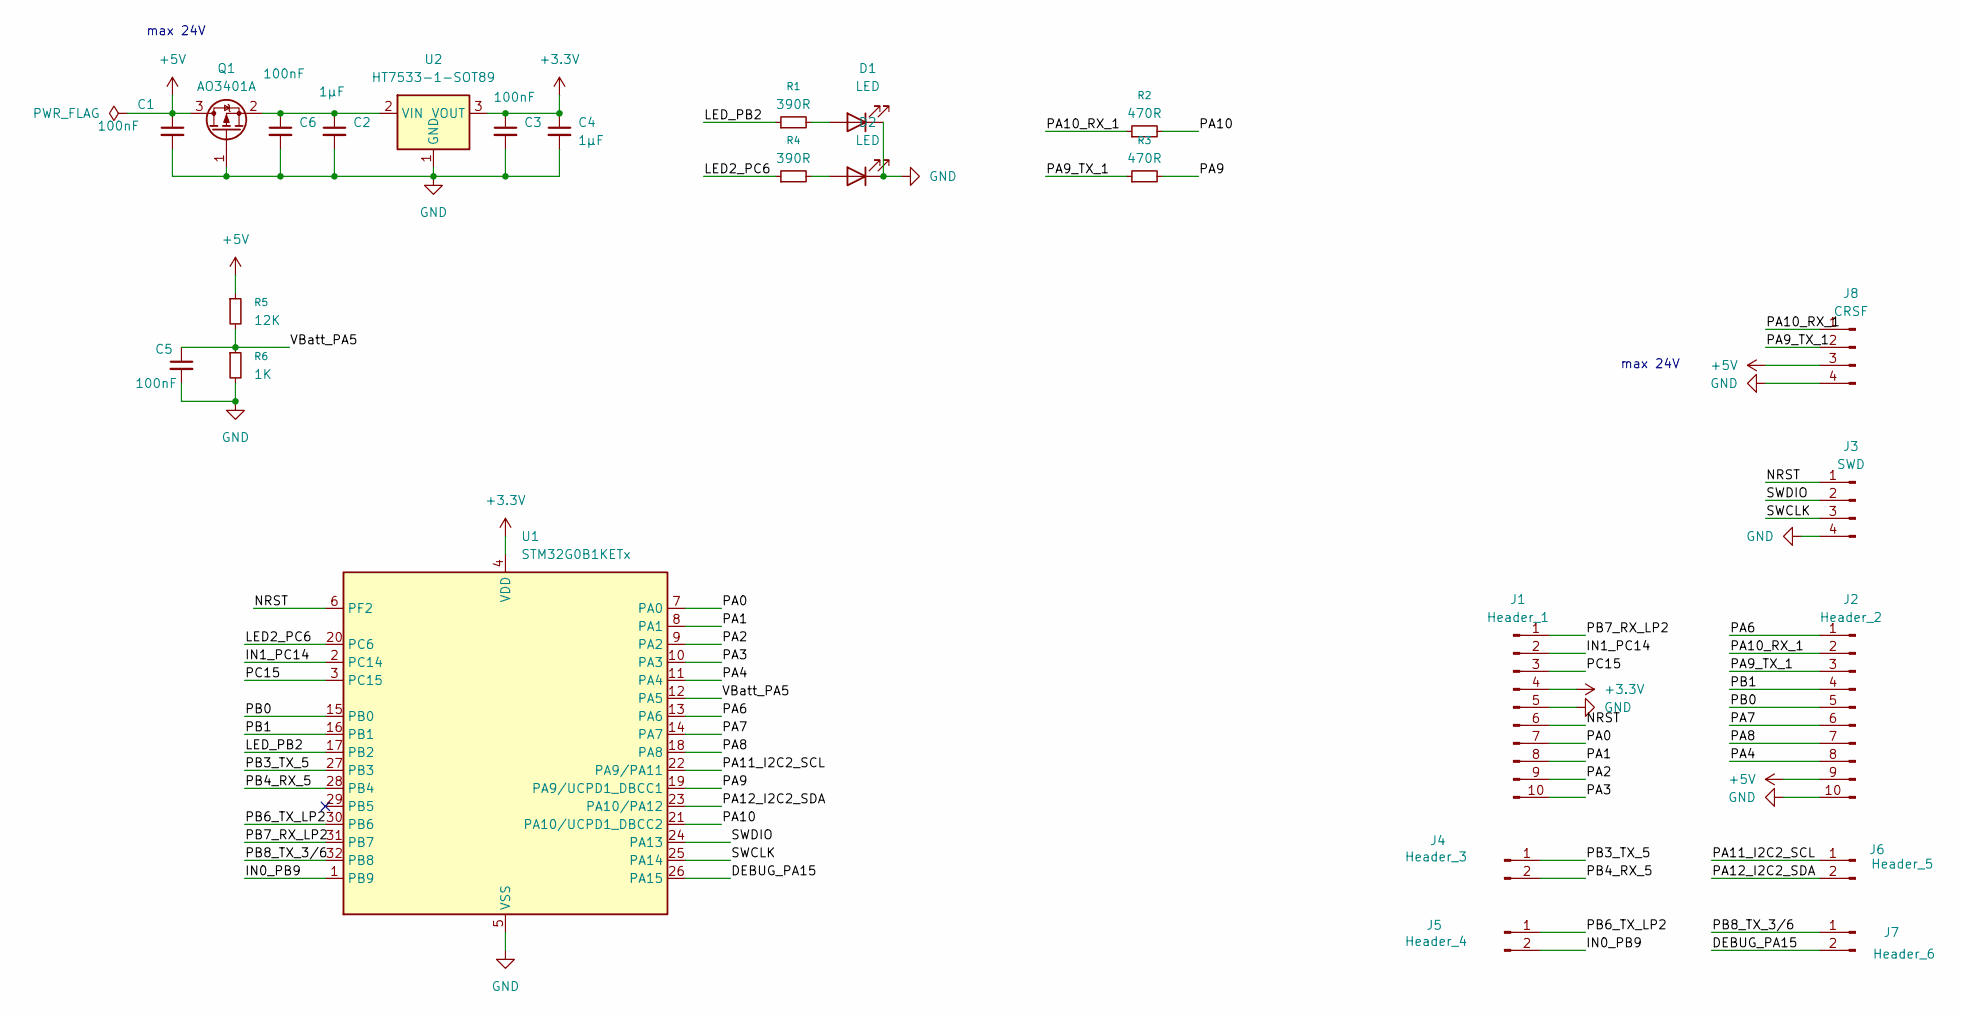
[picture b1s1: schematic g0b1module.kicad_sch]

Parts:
C1, C3, C5, C6: 100nF; C_0805_2012Metric
C2, C4: 1µF; C_0805_2012Metric
D1, D2: LED; LED_0805_2012Metric
J1: Header_1; PinHeader_1x10_P2.54mm_Vertical
J2: Header_2; PinHeader_1x10_P2.54mm_Vertical
J3: SWD; PinHeader_1x04_P2.54mm_Vertical
J4: Header_3; PinHeader_1x02_P2.54mm_Vertical
J5: Header_4; PinHeader_1x02_P2.54mm_Vertical
J6: Header_5; PinHeader_1x02_P2.54mm_Vertical
J7: Header_6; PinHeader_1x02_P2.54mm_Vertical
J8: CRSF; JST_GH_SM04B-GHS-TB_1x04-1MP_P1.25mm_Horizontal
Q1: AO3401A; SOT-23
R1, R4: 390R; R_0805_2012Metric
R2, R3: 470R; R_0805_2012Metric
R5: 12K; R_0805_2012Metric
R6: 1K; R_0805_2012Metric
U1: STM32G0B1KETx; UQFN-32_5x5mm_P0.5mm
U2: HT7533-1-SOT89; SOT-89-3

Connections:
+3.3V: C3.1, C4.1, J1.4, U1.4 (VDD), U2.3 (VOUT)
+5V: C1.1, J2.9, J8.3, Q1.3 (D), R5.1
/DEBUG_PA15: J7.2, U1.26 (PA15)
/IN0_PB9: J5.2, U1.1 (PB9)
/IN1_PC14: J1.2, U1.2 (PC14)
/LED2_PC6: R4.1, U1.20 (PC6)
/LED_PB2: R1.1, U1.17 (PB2)
/NRST: J1.6, J3.1, U1.6 (PF2)
/PA0: J1.7, U1.7 (PA0)
/PA1: J1.8, U1.8 (PA1)
/PA2: J1.9, U1.9 (PA2)
/PA3: J1.10, U1.10 (PA3)
/PA4: J2.8, U1.11 (PA4)
/PA6: J2.1, U1.13 (PA6)
/PA7: J2.6, U1.14 (PA7)
/PA8: J2.7, U1.18 (PA8)
/PA9: R3.2, U1.19 (PA9/UCPD1_DBCC1)
/PA9_TX_1: J2.3, J8.2, R3.1
/PA10: R2.2, U1.21 (PA10/UCPD1_DBCC2)
/PA10_RX_1: J2.2, J8.1, R2.1
/PA11_I2C2_SCL: J6.1, U1.22 (PA9/PA11)
/PA12_I2C2_SDA: J6.2, U1.23 (PA10/PA12)
/PB0: J2.5, U1.15 (PB0)
/PB1: J2.4, U1.16 (PB1)
/PB3_TX_5: J4.1, U1.27 (PB3)
/PB4_RX_5: J4.2, U1.28 (PB4)
/PB6_TX_LP2: J5.1, U1.30 (PB6)
/PB7_RX_LP2: J1.1, U1.31 (PB7)
/PB8_TX_3/6: J7.1, U1.32 (PB8)
/PC15: J1.3, U1.3 (PC15)
/SWCLK: J3.3, U1.25 (PA14)
/SWDIO: J3.2, U1.24 (PA13)
/VBatt_PA5: C5.1, R5.2, R6.1, U1.12 (PA5)
GND: C1.2, C2.2, C3.2, C4.2, C5.2, C6.2, D1.1 (K), D2.1 (K), J1.5, J2.10, J3.4, J8.4, Q1.1 (G), R6.2, U1.5 (VSS), U2.1 (GND)
unnamed: D1.2 (A), R1.2
unnamed: D2.2 (A), R4.2
unnamed: C2.1, C6.1, Q1.2 (S), U2.2 (VIN)

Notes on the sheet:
max 24V
max 24V

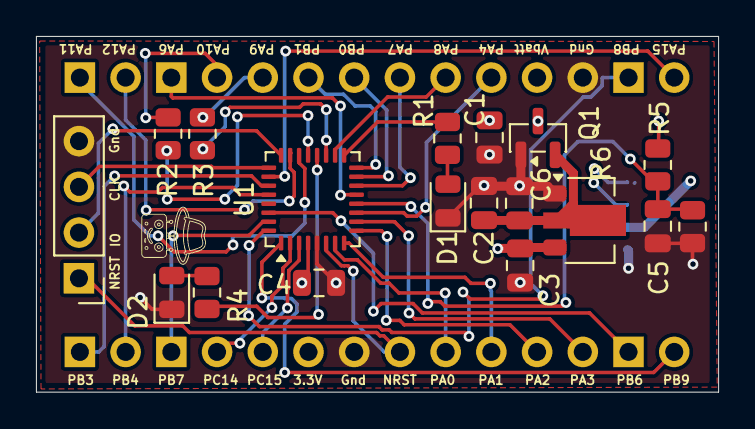
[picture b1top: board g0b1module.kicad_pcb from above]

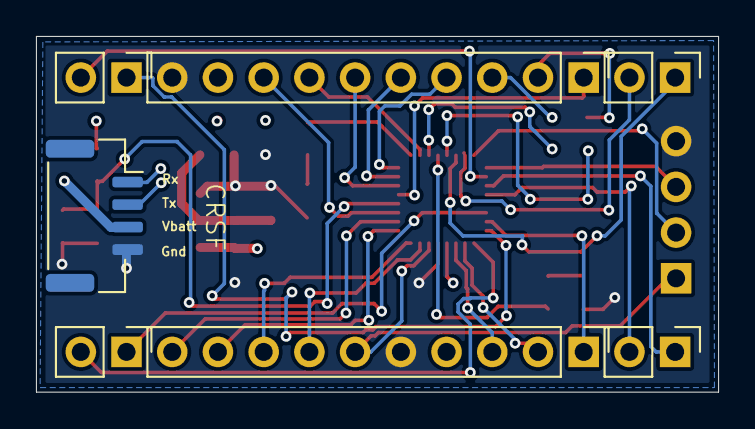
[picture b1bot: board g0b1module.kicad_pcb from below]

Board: 4 copper layers, 37.9 x 19.8 mm, 25 parts (7 on the bottom side), 37 nets.

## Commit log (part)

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2023-10-01 new retro images
2023-10-02 new images
2023-10-03 renamed images
2023-10-14 bldc images
2023-10-16 rename of images
2023-11-22 new bldc document
2023-11-22 Update README.adoc
    CruiseControl
2023-11-22 Update README.adoc
    typo
2023-11-22 images
2023-11-22 Update README.adoc
    syntax
2024-04-01 switched to english version
2024-04-04 added missing files
2024-04-04 wip: update
2024-04-04 added some vintage rc images
2024-04-06 more images
2024-04-07 description of extended crsf protocol
2024-04-07 assembling description of elrs jr module bay adapter
2024-04-07 some more placeholders
2024-04-07 clearified crsf extension
2024-04-07 sectioning
2024-04-08 added images
2024-04-08 added BDC feature list
2024-04-08 toc text
2024-04-08 added images of the BDCs
2024-04-08 more descriptions
2024-04-08 typo
2024-04-10 added images more doc for the varioprop
2024-04-10 added LA trace for elrs jr adapter
2024-04-12 added inmages and description for X9E
2024-05-03 added info for ELRS teamrace / modified
2024-05-03 start 32-channels information
2024-05-04 ESCape32 info
2024-05-04 added VESC info
2024-07-01 added image
2024-07-01 png images
2024-07-01 added schematics
2024-07-01 added spectra
2024-07-02 added spec F14 and Gr module
2024-07-02 Update README.adoc
    added pcb images for variopropNG03
2024-07-12 added elrs_msw
2024-07-18 added target file
2024-07-18 added crsf hs bus target file
2024-07-28 gerber added
2024-08-10 added photos of the hardware extension
2024-10-19 add Target3001 for simple switch
2024-11-25 added images rc720e32
2024-11-25 Update README.adoc for RC720E32
2024-11-25 Update README.adoc: image formats
2024-11-25 added PNG images
2024-12-12 added RC720E32_02 images
2025-01-17 Update README.adoc
    Added Aisler link for Schottel controller
2025-01-17 Update README.adoc
    Updated feature list of Schottel controller
2025-01-17 Update README.adoc
    typo in link
2025-03-16 added rcdesk images
2025-03-16 added png
2025-05-30 added schottel images
2025-05-30 description for cruise controller
2025-05-30 Added gitpod hint
2025-07-16 added new image
2025-09-16 added files
2025-09-17 added seaspotter msw
2025-09-21 added gerber files
2025-10-06 added codespaces images
2025-10-08 added logo images
2025-10-15 logo
2025-10-15 Logos
2025-10-16 Update table of contents settings in README
    Adjusted table of contents levels in README.
2025-10-16 Add OSHWLab hardware designs section to README
    Added section for hardware designs available on OSHWLab.
2025-11-28 Document RC-Desk mini project and pin configuration
    Added details about the RC-Desk mini project, including hardware platform and pin descriptions.
2025-11-28 Clarify pin usage for button and LED
    Updated pin descriptions for button and LED in the README.
2025-11-28 Fix serial debug output pin mapping in README
2025-11-30 Update RC-Desk mini documentation
    Clarified usage of SBUS and CRSF protocols for RC-Desk mini.
2025-12-10 Document RC-Relay32 functionality and use cases
    Added documentation for RC-Relay32, including setup instructions and use cases.
2025-12-15 Fix typos in CRSF-Switch documentation
    Corrected minor typos and formatting in the CRSF-Switch section.
2025-12-18 Document WM STM32G0B1 development board features
    Added information about the WM STM32G0B1 development board and its advantages over the WeAct STM32G031F8.
2025-12-19 added wmg0b1 board
2025-12-19 Add GitHub link for the board in README
    Added a link to the board's GitHub repository for reference.
2025-12-21 Document command `0x13` for intermodule slave set
    Added documentation for command `0x13` to README.
2025-12-31 Document ELRS V4 modifications and build instructions
    Added modifications and instructions for ELRS V4.
2025-12-31 Fix link format for elrs:sumdv3 in README
2026-01-01 Update README with clearer instructions
    Clarified instructions regarding 'super_defines.txt' and modified the wording for better readability.
2026-01-04 Document 32 channels extension for ELRS V4
    Added information about 32 channels extension for ELRS V4 and updated related sections.
2026-01-04 Fix link formatting for 32 channels extension
2026-01-06 cleanup
2026-01-06 edgetx german wmextensions prebuilt firmware
2026-01-07 updated edgetx firmwares
2026-01-08 new edgetx firmware
2026-01-10 Add tip for using expresslrs-configurator
    Added a tip about selecting modifications via the expresslrs-configurator.
2026-01-10 Document 32-Channels extension for EdgeTx
    Added section for 32-Channels extension for CRSF-Protocol and updated links.
2026-01-10 Update README.adoc
    Removed outdated link to firmware repository.
2026-01-10 new edgetx
2026-01-10 edgetx firmware
2026-01-13 Document SFrog 5D Sticks modification for X12S
    Added section for SFrog 5D Sticks modification for FrSky X12S.
2026-01-13 added sfrog document
2026-01-13 Fix typo in SFrog 5D Sticks modification description
2026-01-13 added sfrog docs
2026-01-13 delet pdf
2026-01-13 updated docs
2026-01-14 added test file
2026-01-14 Fix link to SFrog 5D Stick modification document
    Updated the link to the SFrog 5D Stick modification document to point to the GitHub preview.
2026-01-14 Update links in README for touch modifications
2026-01-14 added images to html
2026-01-21 Update README with correct pin descriptions
2026-01-22 Update README with TX16S MK3 and TX15 information
    Added reviews and details for TX16S MK3 and TX15.
2026-01-23 added edgetx prebuilds
2026-01-23 Update README with precompiled EdgeTx builds info
    Added a tip about precompiled EdgeTx builds and their location.
2026-01-25 added tx16smk3
2026-02-01 updated firmware
2026-02-03 fixed sfrog document
2026-02-13 new edgetx versions
2026-03-28 new firmware files
2026-04-03 EdgeTx 2.12 wmextensions
2026-04-17 type, clarification
2026-04-19 corrected rcDesk32mini doc
2026-05-08 edgetx firmware wmextensions update
2026-05-17 Add image for WM STM32G0B1 development board
    Added an image for the WM STM32G0B1 development board.
2026-05-17 Update image path for STM32G0B1 development board
2026-05-17 Update README with relay and serial servo images
    Added images and descriptions for relays and serial servos in the README.
2026-05-17 Update serial servos section with CRSF reference
    Added reference to CRSF serial servo in the serial servos section and included additional links for context.
2026-05-19 Add warning about no AI generated code
    Added a warning note about AI-generated code.
2026-06-14 new edgetx prebuilds
2026-06-16 updated edgetx fw
2026-06-17 Enhance ESCape32 section in README
    Updated features and project information for ESCape32.
2026-06-17 Document self-balancing robot project 'Mortimer'
    Added a section about the self-balancing inverted pendulum robot project 'Mortimer', detailing its design, components, and modifications made to the INav software.
2026-06-17 Add video link for serial-servo application
    Added a link to a video demonstrating the application of the serial-servo as a sailboat winch.
2026-06-17 Fix duplicate application link in README
    Removed duplicate link for sailboat winch application in README.
2026-06-21 Update README with firmware compilation instructions
    Added instructions for compiling firmware and flashing process.
2026-06-24 Enhance MultiSwitch documentation with new input option
    Updated the Super simple MultiSwitch section to include Graupner/SumDV3 as an input option and corrected minor typos.
2026-06-25 Enhance README with features and CRSF protocol details
    Added details about controllability, dynamic power, and CRSF protocol realms.
2026-06-25 Update README with OpenI6X uninverted mode details
    Updated the note about the uninverted mode for OpenI6X, specifying the change from compile-time to runtime setting after version 2.1. Corrected the reference label for the FlySky-I6X section.
2026-06-25 Update README with changes for ELRS V4
    Removed outdated tip regarding configurator modifications and updated the list of unnecessary modifications for V4.
2026-06-28 Improve README.adoc content for ESCape32 firmware
    Updated descriptions for ESCape32 firmware, correcting grammar and enhancing clarity.
